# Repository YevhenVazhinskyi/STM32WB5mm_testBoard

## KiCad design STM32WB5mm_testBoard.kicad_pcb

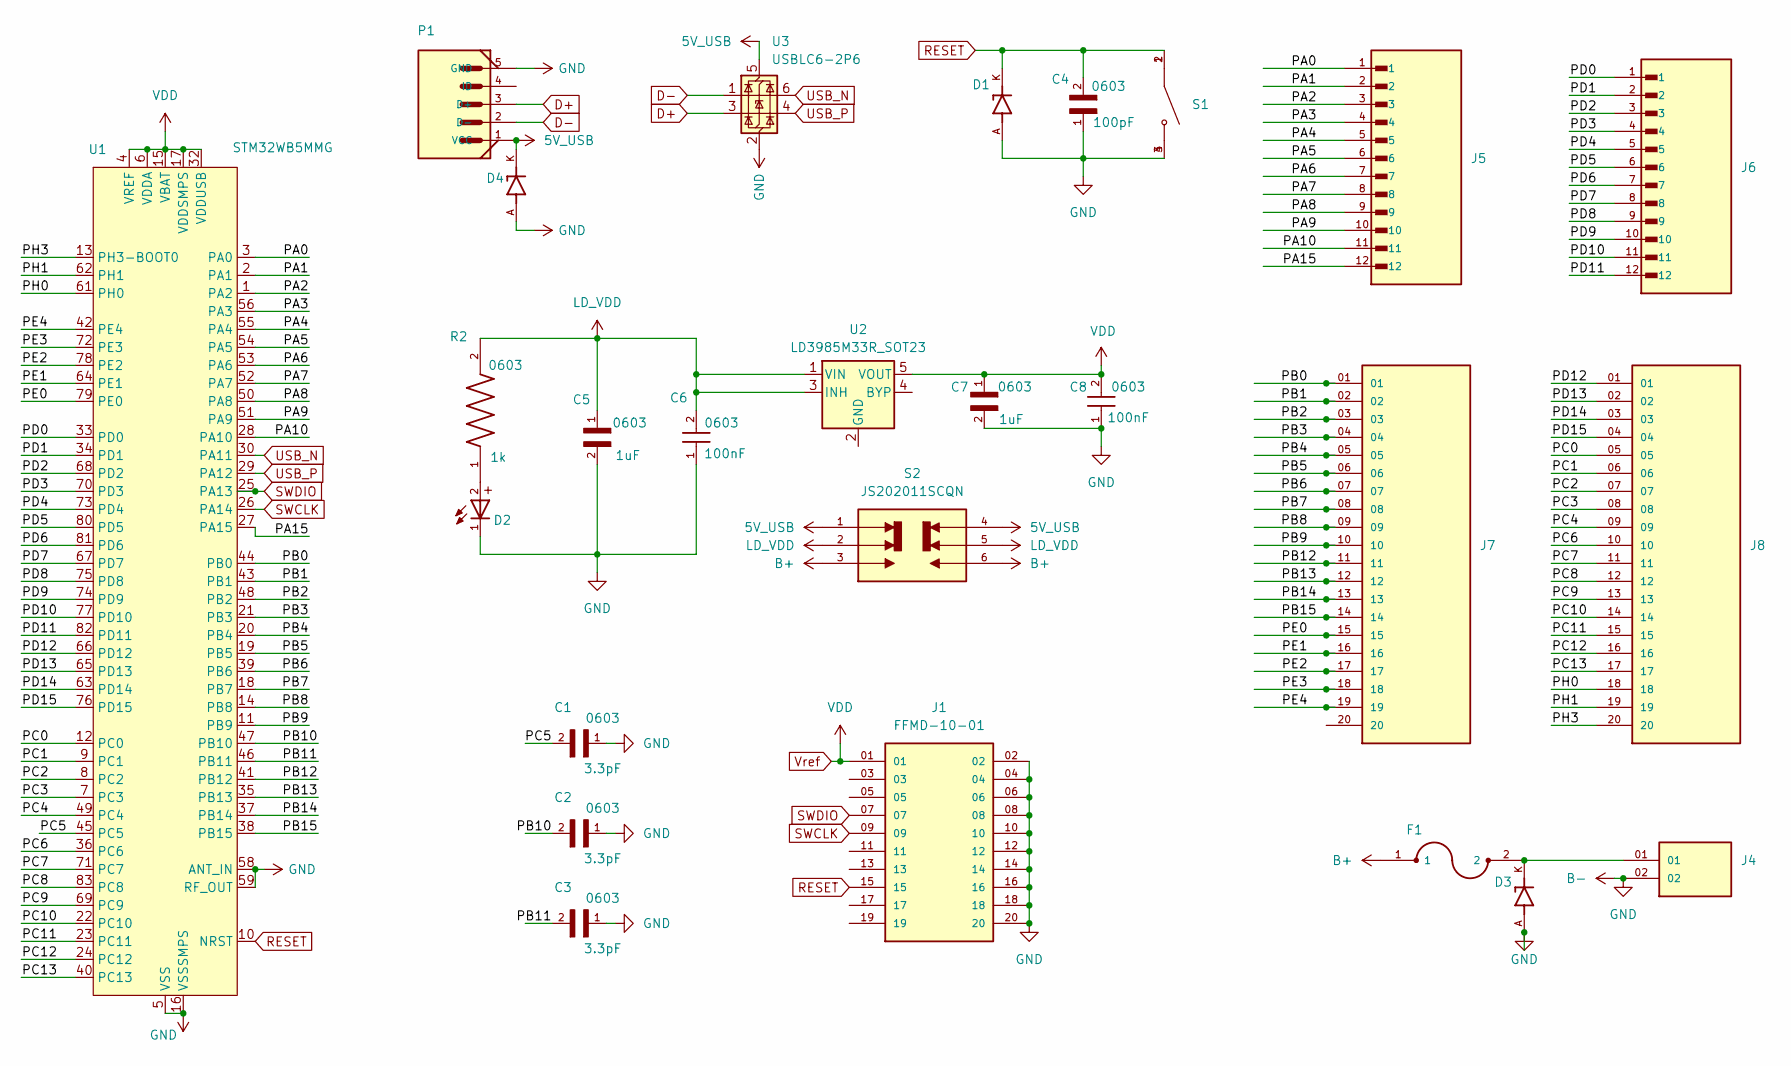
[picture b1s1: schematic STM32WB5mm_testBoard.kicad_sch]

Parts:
C1, C2, C3: 0603; CAPC1608X90
C4: GRM0335C1H101JA01D; CAPC0603X33N
C5, C7: GRT188R61E105KE13D; CAPC1608X9N
C6, C8: WCAP-CSGP_0603; WCAP-CSGP_0603_R
D1, D3, D4: PESD5V0S1UL_315; DIO_PESD5V0S1UL_315; PARTREV 15 January 2020
D2: WL-SMCW_0603
F1: MF-MSMF050-2; FUSM4632X85
J1: FFMD-10-01; SAMTEC_FFMD-10-01; PARTREV C
J4: MTMM-102-05-G-S-175; SAMTEC_MTMM-102-05-G-S-175
J5, J6: M20-9991246; HARWIN_M20-9991246
J7, J8: ZW-20-09-L-S-250-320; SAMTEC_ZW-20-09-L-S-250-320; PARTREV R
P1: 0475890001; MOLEX_0475890001
R2: CHP0603-FX-1001ELF; RESC1608X55N
S1: PTS526_SM08_SMTR2_LFS; SW_PTS526_SM08_SMTR2_LFS; PARTREV 20 mar 19
S2: JS202011SCQN; SW_JS202011SCQN; PARTREV 26 May 22
U1: STM32WB5MMG; ST-SiP-LGA-86-11x7.3mm
U2: LD3985M33R_SOT23; SOT-23-5
U3: USBLC6-2P6; SOT-666

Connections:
5V_USB: D4.K, P1.1 (VCC), S2.1, S2.4, U3.5 (VBUS)
/PA0: J5.1, U1.3 (PA0)
/PA1: J5.2, U1.2 (PA1)
/PA2: J5.3, U1.1 (PA2)
/PA3: J5.4, U1.56 (PA3)
/PA4: J5.5, U1.55 (PA4)
/PA5: J5.6, U1.54 (PA5)
/PA6: J5.7, U1.53 (PA6)
/PA7: J5.8, U1.52 (PA7)
/PA8: J5.9, U1.50 (PA8)
/PA9: J5.10, U1.51 (PA9)
/PA10: J5.11, U1.28 (PA10)
/PA15: J5.12, U1.27 (PA15)
/PB0: J7.01, U1.44 (PB0)
/PB1: J7.02, U1.43 (PB1)
/PB2: J7.03, U1.48 (PB2)
/PB3: J7.04, U1.21 (PB3)
/PB4: J7.05, U1.20 (PB4)
/PB5: J7.06, U1.19 (PB5)
/PB6: J7.07, U1.39 (PB6)
/PB7: J7.08, U1.18 (PB7)
/PB8: J7.09, U1.14 (PB8)
/PB9: J7.10, U1.11 (PB9)
/PB10: C2.2, U1.47 (PB10)
/PB11: C3.2, U1.46 (PB11)
/PB12: J7.11, U1.41 (PB12)
/PB13: J7.12, U1.35 (PB13)
/PB14: J7.13, U1.37 (PB14)
/PB15: J7.14, U1.38 (PB15)
/PC0: J8.05, U1.12 (PC0)
/PC1: J8.06, U1.9 (PC1)
/PC2: J8.07, U1.8 (PC2)
/PC3: J8.08, U1.7 (PC3)
/PC4: J8.09, U1.49 (PC4)
/PC5: C1.2, U1.45 (PC5)
/PC6: J8.10, U1.36 (PC6)
/PC7: J8.11, U1.71 (PC7)
/PC8: J8.12, U1.83 (PC8)
/PC9: J8.13, U1.69 (PC9)
/PC10: J8.14, U1.22 (PC10)
/PC11: J8.15, U1.23 (PC11)
/PC12: J8.16, U1.24 (PC12)
/PC13: J8.17, U1.40 (PC13)
/PD0: J6.1, U1.33 (PD0)
/PD1: J6.2, U1.34 (PD1)
/PD2: J6.3, U1.68 (PD2)
/PD3: J6.4, U1.70 (PD3)
/PD4: J6.5, U1.73 (PD4)
/PD5: J6.6, U1.80 (PD5)
/PD6: J6.7, U1.81 (PD6)
/PD7: J6.8, U1.67 (PD7)
/PD8: J6.9, U1.75 (PD8)
/PD9: J6.10, U1.74 (PD9)
/PD10: J6.11, U1.77 (PD10)
/PD11: J6.12, U1.82 (PD11)
/PD12: J8.01, U1.66 (PD12)
/PD13: J8.02, U1.65 (PD13)
/PD14: J8.03, U1.63 (PD14)
/PD15: J8.04, U1.76 (PD15)
/PE0: J7.15, U1.79 (PE0)
/PE1: J7.16, U1.64 (PE1)
/PE2: J7.17, U1.78 (PE2)
/PE3: J7.18, U1.72 (PE3)
/PE4: J7.19, U1.42 (PE4)
/PH0: J8.18, U1.61 (PH0)
/PH1: J8.19, U1.62 (PH1)
/PH3: J8.20, U1.13 (PH3-BOOT0)
B+: F1.1, S2.3, S2.6
B-: C1.1, C2.1, C3.1, C4.1, C5.2, C6.1, C7.2, C8.1, D1.A, D2.1, D3.A, D4.A, J1.02, J1.04, J1.06, J1.08, J1.10, J1.12, J1.14, J1.16, J1.18, J1.20, J4.02, P1.5 (GND), S1.3, S1.4, U1.5 (VSS), U1.16 (VSSSMPS), U1.31 (VSS), U1.57 (VSS), U1.58 (ANT_IN), U1.59 (RF_OUT), U1.60 (VSS), U1.84 (VSS), U1.86 (VSS), U3.2 (GND)
D+: P1.3 (D+), U3.3 (I/O2)
D-: P1.2 (D-), U3.1 (I/O1)
LD_VDD: C5.1, C6.2, R2.2, S2.2, S2.5, U2.1 (VIN), U2.3 (INH)
unnamed: D2.2, R2.1
unnamed: D3.K, F1.2, J4.01
RESET: C4.2, D1.K, J1.15, S1.1, S1.2, U1.10 (NRST)
SWCLK: J1.09, U1.26 (PA14)
SWDIO: J1.07, U1.25 (PA13)
USB_N: U1.30 (PA11), U3.6 (I/O1)
USB_P: U1.29 (PA12), U3.4 (I/O2)
Vref: C7.1, C8.2, J1.01, U1.4 (VREF), U1.6 (VDDA), U1.15 (VBAT), U1.17 (VDDSMPS), U1.32 (VDDUSB), U2.5 (VOUT)

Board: 2 copper layers, 26 parts (0 on the bottom side), 80 nets, no tracks yet.

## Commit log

2025-04-13 first commit project
